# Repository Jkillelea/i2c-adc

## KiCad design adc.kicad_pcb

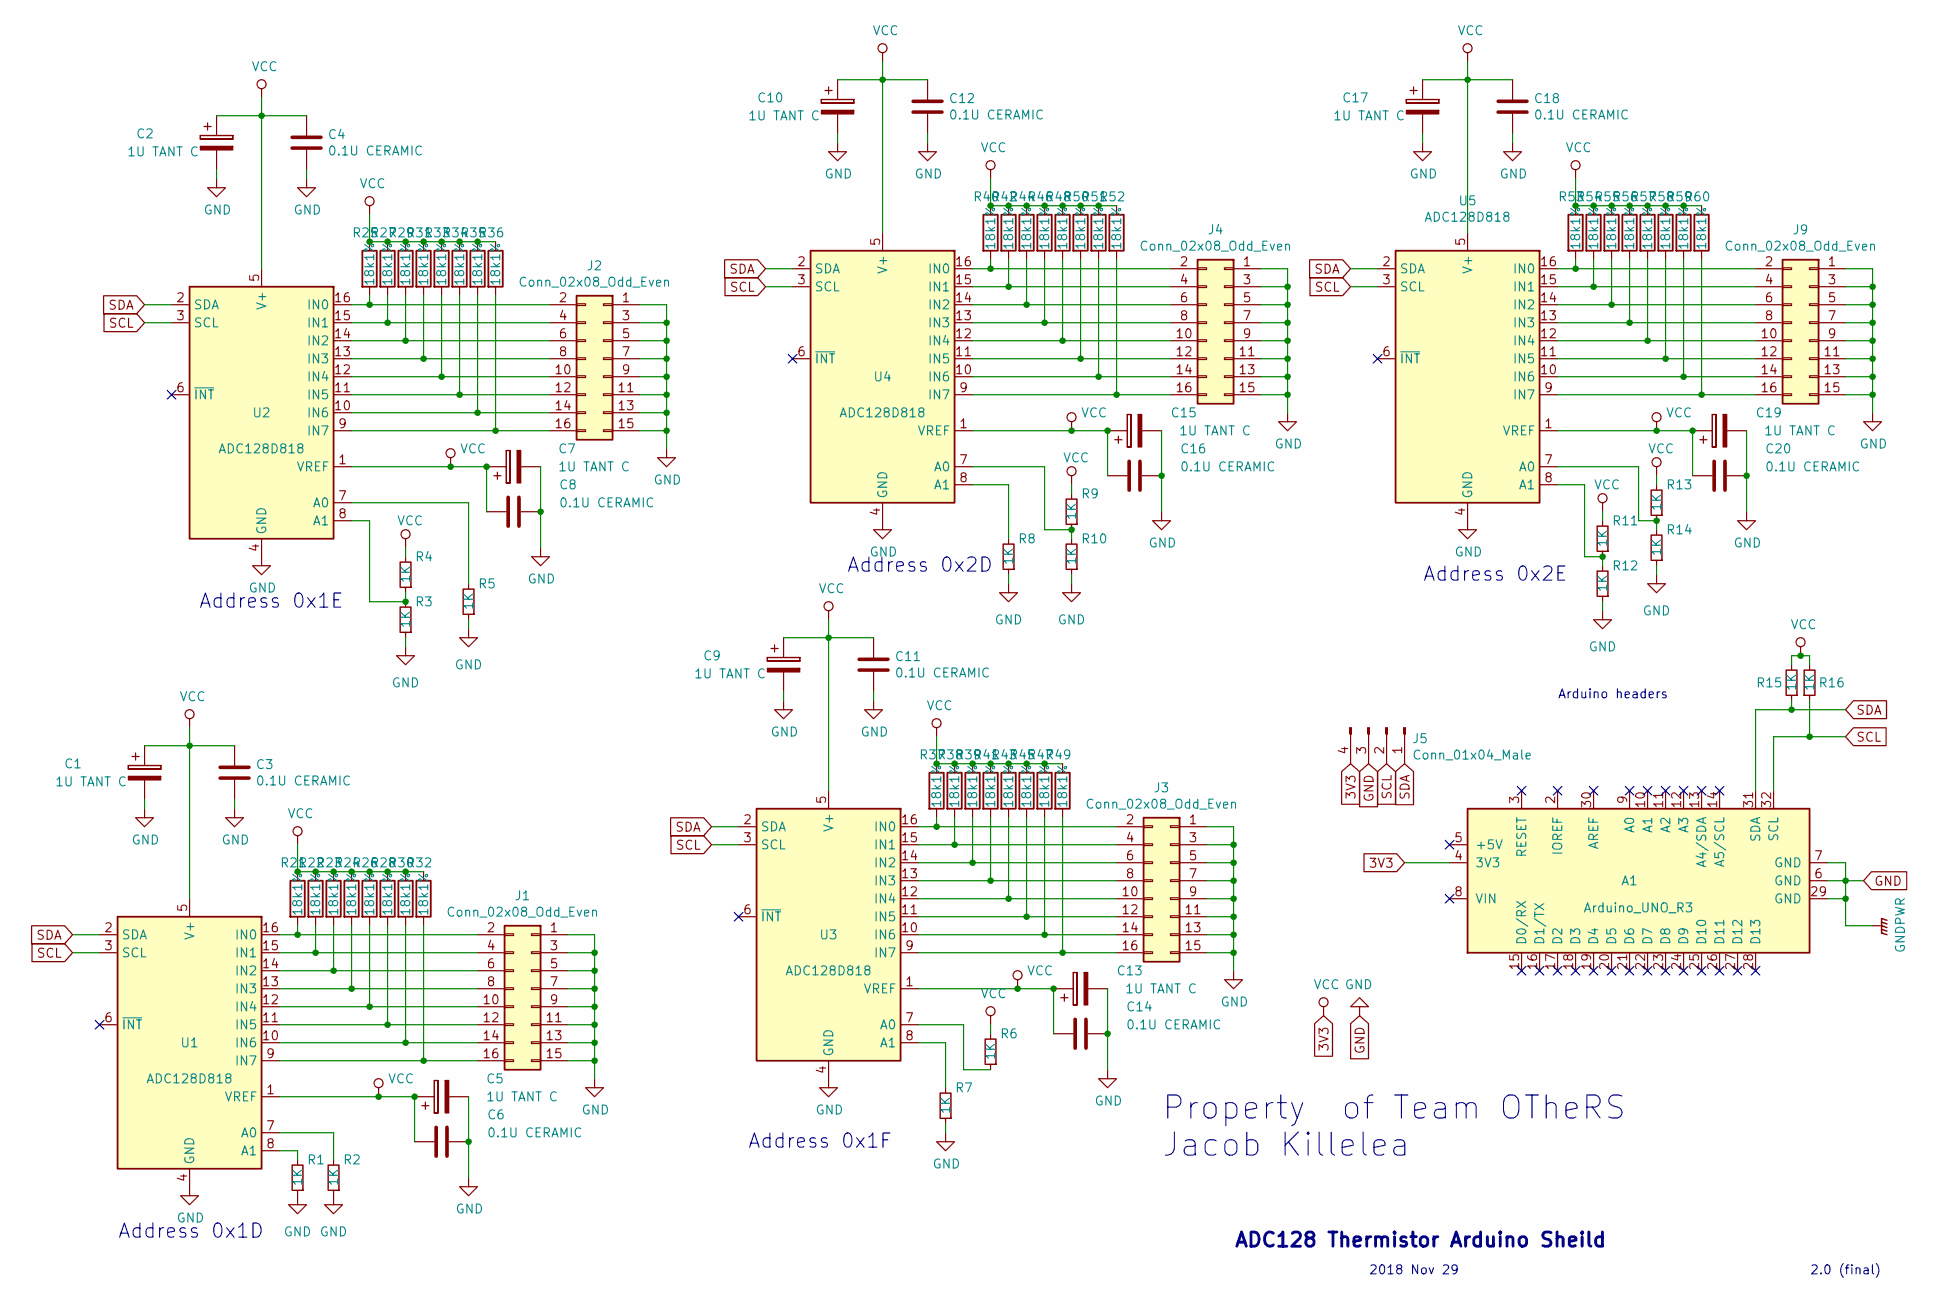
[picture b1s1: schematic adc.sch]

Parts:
A1: Arduino_UNO_R3
C1, C2, C5, C7, C9, C10, C13, C15, C17, C19: 1U TANT C; CP_EIA-3216-18_Kemet-A_Pad1.58x1.35mm_HandSolder
C3, C4, C6, C8, C11, C12, C14, C16, C18, C20: 0.1U CERAMIC; C_1210_3225Metric_Pad1.42x2.65mm_HandSolder
J1, J2, J3, J4, J9: Conn_02x08_Odd_Even; PinHeader_2x08_P2.54mm_Vertical
J5: Conn_01x04_Male; PinHeader_1x04_P2.54mm_Vertical
R1, R2, R3, R4, R5, R6, R7, R8, R9, R10, R11, R12, R13, R14, R15, R16: 1K; R_0805_2012Metric_Pad1.15x1.40mm_HandSolder
R21, R22, R23, R24, R25, R26, R27, R28, R29, R30, R31, R32, R33, R34, R35, R36, R37, R38, R39, R40, R41, R42, R43, R44, R45, R46, R47, R48, R49, R50, R51, R52, R53, R54, R55, R56, R57, R58, R59, R60: 18k1%; R_1206_3216Metric_Pad1.42x1.75mm_HandSolder
U1, U2, U3, U4, U5: ADC128D818; TSSOP-16_4.4x5mm_P0.65mm

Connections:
3V3: A1.4 (3V3), C1.1, C2.1, C3.1, C4.1, C5.1, C6.2, C7.1, C8.2, C9.1, C10.1, C11.1, C12.1, C13.1, C14.2, C15.1, C16.2, C17.1, C18.1, C19.1, C20.2, J5.4, R4.2, R6.2, R9.2, R11.2, R13.2, R15.2, R16.2, R21.1, R22.1, R23.1, R24.1, R25.1, R26.1, R27.1, R28.1, R29.1, R30.1, R31.1, R32.1, R33.1, R34.1, R35.1, R36.1, R37.1, R38.1, R39.1, R40.1, R41.1, R42.1, R43.1, R44.1, R45.1, R46.1, R47.1, R48.1, R49.1, R50.1, R51.1, R52.1, R53.1, R54.1, R55.1, R56.1, R57.1, R58.1, R59.1, R60.1, U1.1 (VREF), U1.5 (V+), U2.1 (VREF), U2.5 (V+), U3.1 (VREF), U3.5 (V+), U4.1 (VREF), U4.5 (V+), U5.1 (VREF), U5.5 (V+)
GND: A1.6 (GND), A1.7 (GND), A1.29 (GND), C1.2, C2.2, C3.2, C4.2, C5.2, C6.1, C7.2, C8.1, C9.2, C10.2, C11.2, C12.2, C13.2, C14.1, C15.2, C16.1, C17.2, C18.2, C19.2, C20.1, J1.1, J1.3, J1.5, J1.7, J1.9, J1.11, J1.13, J1.15, J2.1, J2.3, J2.5, J2.7, J2.9, J2.11, J2.13, J2.15, J3.1, J3.3, J3.5, J3.7, J3.9, J3.11, J3.13, J3.15, J4.1, J4.3, J4.5, J4.7, J4.9, J4.11, J4.13, J4.15, J5.3, J9.1, J9.3, J9.5, J9.7, J9.9, J9.11, J9.13, J9.15, R1.1, R2.1, R3.1, R5.1, R7.1, R8.1, R10.1, R12.1, R14.1, U1.4 (GND), U2.4 (GND), U3.4 (GND), U4.4 (GND), U5.4 (GND)
unnamed: J1.2, R21.2, U1.16 (IN0)
unnamed: J1.4, R22.2, U1.15 (IN1)
unnamed: J1.6, R23.2, U1.14 (IN2)
unnamed: J1.8, R24.2, U1.13 (IN3)
unnamed: J1.10, R26.2, U1.12 (IN4)
unnamed: J1.12, R28.2, U1.11 (IN5)
unnamed: J1.14, R30.2, U1.10 (IN6)
unnamed: J1.16, R32.2, U1.9 (IN7)
unnamed: J2.2, R25.2, U2.16 (IN0)
unnamed: J2.4, R27.2, U2.15 (IN1)
unnamed: J2.6, R29.2, U2.14 (IN2)
unnamed: J2.8, R31.2, U2.13 (IN3)
unnamed: J2.10, R33.2, U2.12 (IN4)
unnamed: J2.12, R34.2, U2.11 (IN5)
unnamed: J2.14, R35.2, U2.10 (IN6)
unnamed: J2.16, R36.2, U2.9 (IN7)
unnamed: J3.2, R37.2, U3.16 (IN0)
unnamed: J3.4, R38.2, U3.15 (IN1)
unnamed: J3.6, R39.2, U3.14 (IN2)
unnamed: J3.8, R41.2, U3.13 (IN3)
unnamed: J3.10, R43.2, U3.12 (IN4)
unnamed: J3.12, R45.2, U3.11 (IN5)
unnamed: J3.14, R47.2, U3.10 (IN6)
unnamed: J3.16, R49.2, U3.9 (IN7)
unnamed: J4.2, R40.2, U4.16 (IN0)
unnamed: J4.4, R42.2, U4.15 (IN1)
unnamed: J4.6, R44.2, U4.14 (IN2)
unnamed: J4.8, R46.2, U4.13 (IN3)
unnamed: J4.10, R48.2, U4.12 (IN4)
unnamed: J4.12, R50.2, U4.11 (IN5)
unnamed: J4.14, R51.2, U4.10 (IN6)
unnamed: J4.16, R52.2, U4.9 (IN7)
unnamed: J9.2, R53.2, U5.16 (IN0)
unnamed: J9.4, R54.2, U5.15 (IN1)
unnamed: J9.6, R55.2, U5.14 (IN2)
unnamed: J9.8, R56.2, U5.13 (IN3)
unnamed: J9.10, R57.2, U5.12 (IN4)
unnamed: J9.12, R58.2, U5.11 (IN5)
unnamed: J9.14, R59.2, U5.10 (IN6)
unnamed: J9.16, R60.2, U5.9 (IN7)
unnamed: R1.2, U1.8 (A1)
unnamed: R2.2, U1.7 (A0)
unnamed: R3.2, R4.1, U2.8 (A1)
unnamed: R5.2, U2.7 (A0)
unnamed: R6.1, U3.7 (A0)
unnamed: R7.2, U3.8 (A1)
unnamed: R8.2, U4.8 (A1)
unnamed: R9.1, R10.2, U4.7 (A0)
unnamed: R11.1, R12.2, U5.8 (A1)
unnamed: R13.1, R14.2, U5.7 (A0)
SCL: A1.32 (SCL), J5.2, R16.1, U1.3 (SCL), U2.3 (SCL), U3.3 (SCL), U4.3 (SCL), U5.3 (SCL)
SDA: A1.31 (SDA), J5.1, R15.1, U1.2 (SDA), U2.2 (SDA), U3.2 (SDA), U4.2 (SDA), U5.2 (SDA)

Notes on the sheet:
Arduino headers
ADC128 Thermistor Arduino Sheild
2018 Nov 29
2.0 (final)
Property of Team OTheRS Jacob Killelea
Address 0x1D
Address 0x1E
Address 0x1F
Address 0x2D
Address 0x2E

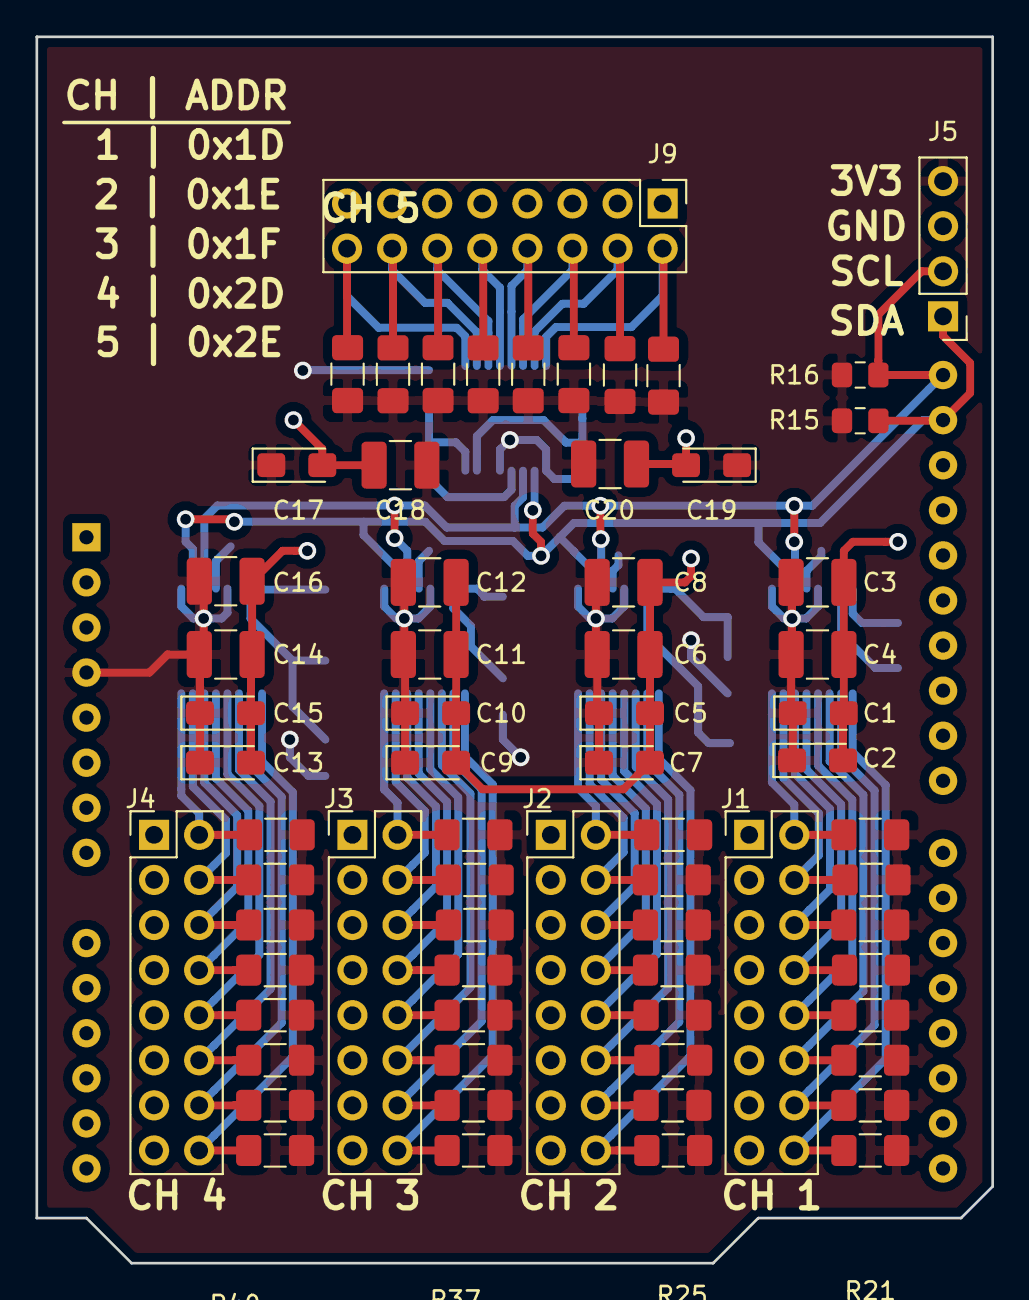
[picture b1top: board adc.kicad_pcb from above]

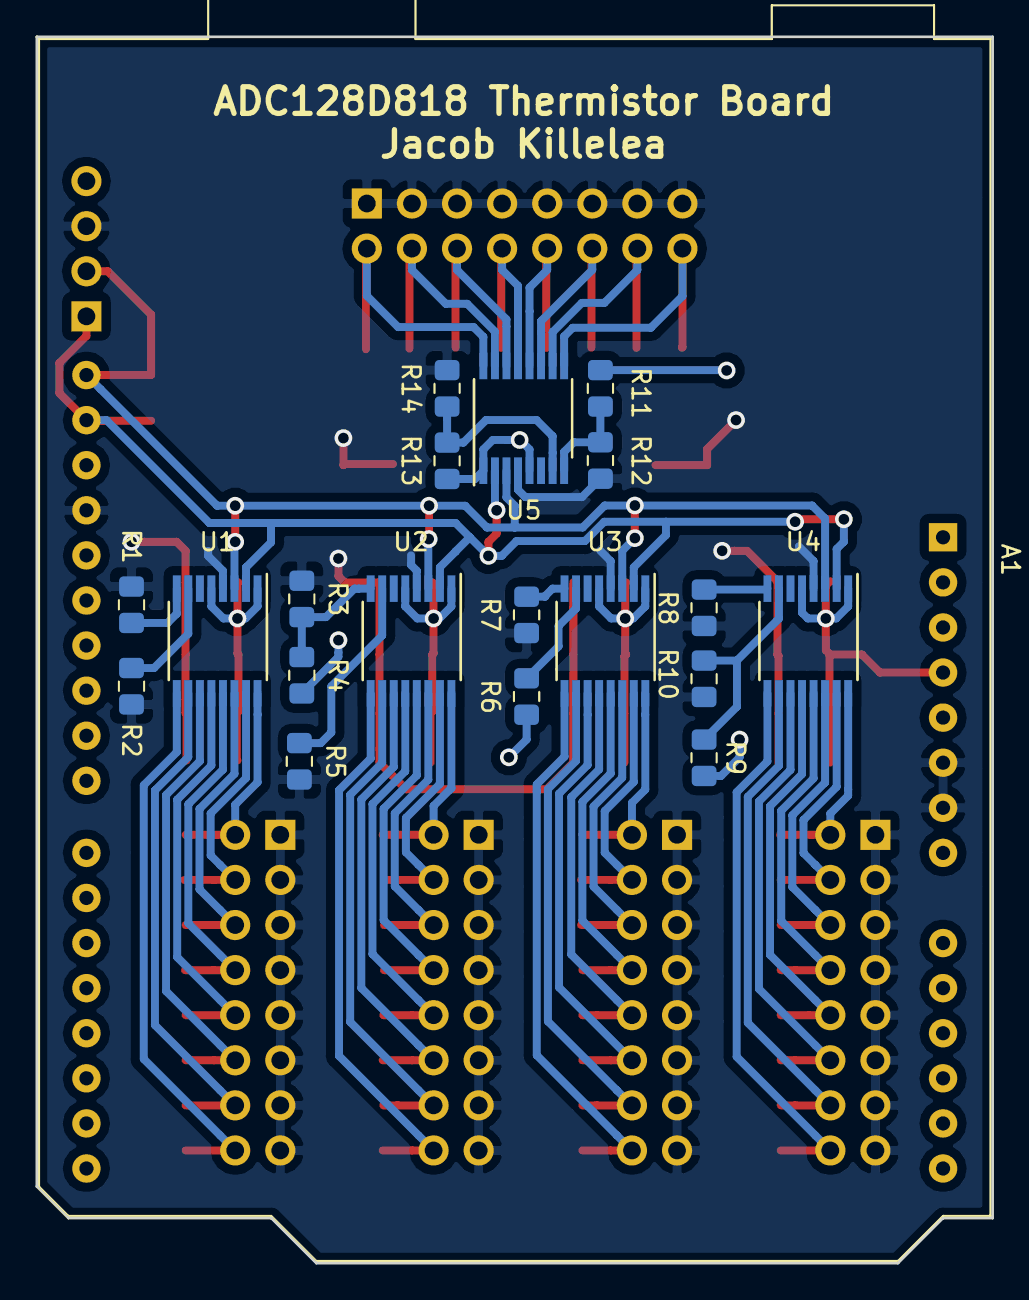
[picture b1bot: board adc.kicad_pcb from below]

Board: 2 copper layers, 53.8 x 69.1 mm, 88 parts (20 on the bottom side), 54 nets.

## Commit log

2018-11-19 first
2018-11-19 footprints
2018-11-19 rev 0
2018-11-20 misc
2018-11-20 misc cleanup
2018-11-20 reduce the number of electrolytic capacitors, improve routing
2018-11-21 change electrolytics to caps, ceramics 1206 -> 1210
2018-11-24 pre-merge
2018-11-27 moved
2018-11-30 updates + printout pdf
2018-11-30 misc + pictures
2018-12-04 new images
2019-01-16 first commit of 5x design. Main components placed. Capacitors are TODO
2019-01-16 18k resistors placed, 1k nearly all placed
2019-01-17 change tantalum cap footprint to Kemet C
2019-01-17 finished placing resistors
2019-01-17 i2c lines
2019-01-17 adjust address resitors
2019-01-17 place ceramic caps (switch to 0805?)
2019-01-17 more routing, fill zones
2019-01-23 Replaced female 2x8 headers with male. Female makes more sense on the thermistors
2019-01-26 add i2c pullup resistors
2019-01-26 silkscreen
2019-01-30 PCBs ordered
2019-01-30 mark schematic as V2 final
2019-02-08 reroute with ITLL design rule tolerances. Switched this one to metric
2019-02-08 fix some remaining track widths
2019-02-22 update trace width after ITLL CNC cutting and correct error causing chip 0x1F to show up as 0x35
2019-02-22 renerate gerbers
2019-04-23 commit going to GA
